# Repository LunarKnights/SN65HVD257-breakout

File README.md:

# Jetson CAN interface board
This board may be used to gain access to the CAN buses on the Jetson TX2 board, which aren't exposed on the carrier board we're currently using.
It mates in between the carrier board and the Jetson TX2, passing through all the connections, but tapping some lines off of the CAN pins and power supply to use in the SN65HVD256D CAN transceivers.
The CAN transceivers act essentially like level shifters, converting from the 3.3 V signals on the CAN RX/TX pins on the Jetson TX2 into the 5 V differential signal used in CAN.

`bom.xls` contains an Excel ordering list that should be usable at Mouser to reorder all the components except for the Samtec connectors.
Those need to be ordered off of the Samtec website, using the exact part names from the design.

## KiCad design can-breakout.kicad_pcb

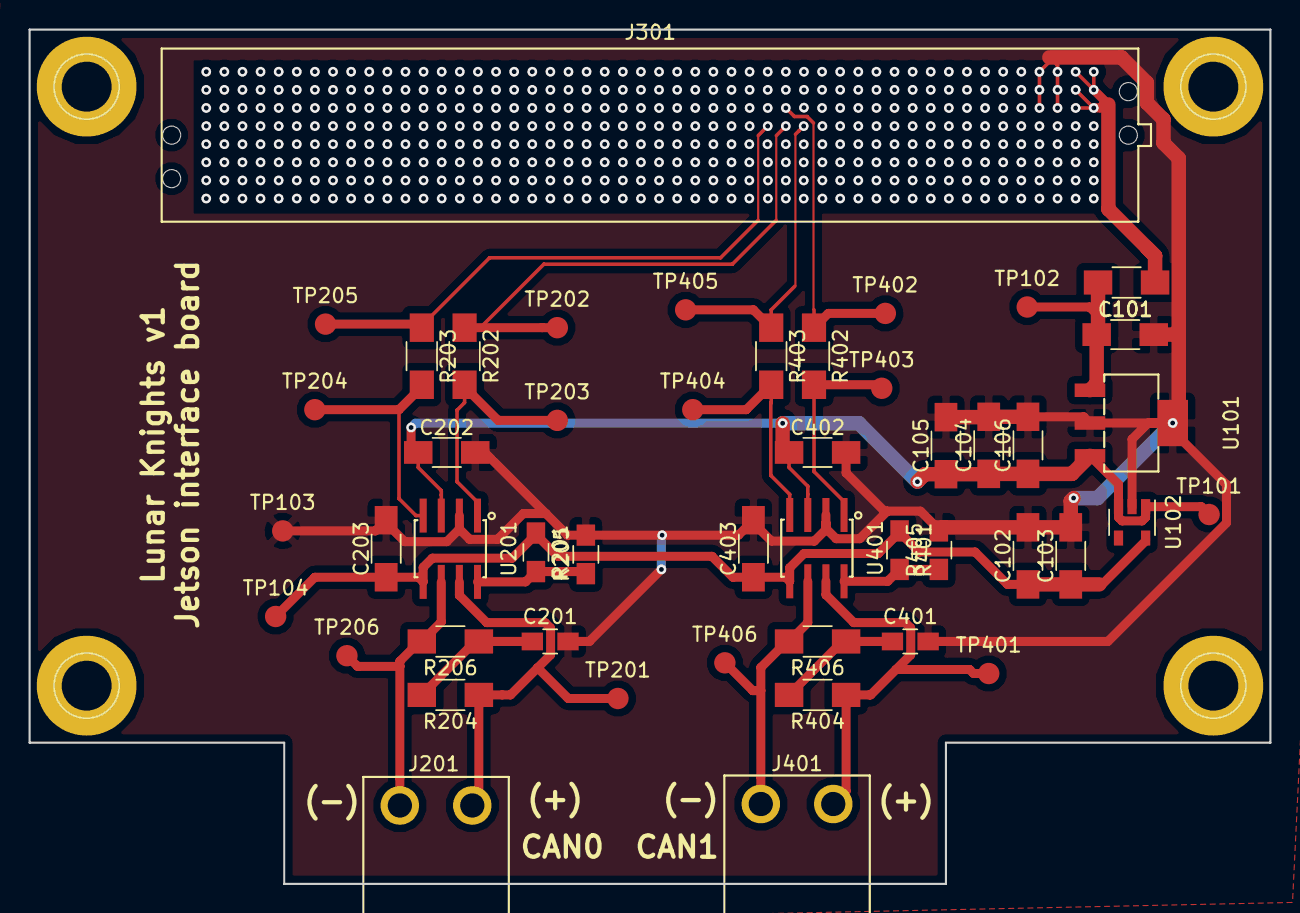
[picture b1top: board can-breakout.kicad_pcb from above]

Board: 2 copper layers, 87.0 x 59.9 mm, 49 parts (1 on the bottom side), 405 nets.

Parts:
C101, C102, C104, C105: 10u; C_1206_HandSoldering
C103, C106, C202, C203, C402, C403: 0u1; C_1206_HandSoldering
C201, C401: 10n; C_0805_HandSoldering
J201, J401: Screw_Terminal_01x02; 39532-0002
J301: SEAM-50-02.0-S-08-2-A-K-TR-ND; SEAM-50-02.0-S-08-2-A-K-TR
J302: SEAF-50-05.0-S-08-2-A-K-TR
L101: Ferrite; R_1206_HandSoldering
R201, R401: DNC; R_0805_HandSoldering
R202, R203, R402, R403: 4k7; R_1206_HandSoldering
R204, R206, R404, R406: 60; R_1206_HandSoldering
R205, R405: 10k; R_0805_HandSoldering
TP101, TP102, TP103, TP104, TP201, TP202, TP203, TP204, TP205, TP206, TP401, TP402, TP403, TP404, TP405, TP406: TEST; Measurement_Point_Round-SMD-Pad_Small
U101: UA78M05IDCYR; TI_SOT-223-4
U102: MIC5365-3.3YD5-TR; SOT-23-5
U201, U401: SN65HVD256; TI_SOIC8

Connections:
+3V3: C102.1, C103.1, C203.1, C403.1, R201.1, R401.1, TP104.1, U102.5, U201.5, U401.5
+5V: C104.1, C105.1, C106.1, C202.1, C402.1, TP101.1, U101.3, U102.1, U102.3, U201.3, U401.3
/CONNECTOR/CAN0_RX: J301.D19, J302.D19, R203.1, TP205.1
/CONNECTOR/CAN0_TX: J301.D18, J302.D18, R202.1, TP202.1
/CONNECTOR/CAN1_RX: J301.D17, J302.D17, R403.1, TP405.1
/CONNECTOR/CAN1_TX: J301.C18, J302.C18, R402.1, TP402.1
/CONNECTOR/VSUPPLY: J301.A1, J301.A2, J301.B1, J301.B2, J301.C1, J301.C2, J302.A1, J302.A2, J302.B1, J302.B2, J302.C1, J302.C2, L101.1
GND: C101.2, C102.2, C103.2, C104.2, C105.2, C106.2, C201.2, C202.2, C203.2, C401.2, C402.2, C403.2, J301.A3, J301.A4, J301.B3, J301.B4, J301.C3, J301.C4, J302.A3, J302.A4, J302.B3, J302.B4, J302.C3, J302.C4, R205.2, R405.2, TP103.1, U101.2, U101.4, U102.2, U201.2, U401.2
unnamed: C101.1, L101.2, TP102.1, U101.1
unnamed: C201.1, R204.2, R206.1
unnamed: C401.1, R404.2, R406.1
unnamed: J201.1, R204.1, TP201.1, U201.7
unnamed: J201.2, R206.2, TP206.1, U201.6
unnamed: J301.A5, J302.A5
unnamed: J301.A6, J302.A6
unnamed: J301.A7, J302.A7
unnamed: J301.A8, J302.A8
unnamed: J301.A9, J302.A9
unnamed: J301.A10, J302.A10
unnamed: J301.A11, J302.A11
unnamed: J301.A12, J302.A12
unnamed: J301.A13, J302.A13
unnamed: J301.A14, J302.A14
unnamed: J301.A15, J302.A15
unnamed: J301.A16, J302.A16
unnamed: J301.A17, J302.A17
unnamed: J301.A18, J302.A18
unnamed: J301.A19, J302.A19
unnamed: J301.A20, J302.A20
unnamed: J301.A21, J302.A21
unnamed: J301.A22, J302.A22
unnamed: J301.A23, J302.A23
unnamed: J301.A24, J302.A24
unnamed: J301.A25, J302.A25
unnamed: J301.A26, J302.A26
unnamed: J301.A27, J302.A27
unnamed: J301.A28, J302.A28
unnamed: J301.A29, J302.A29
unnamed: J301.A30, J302.A30
unnamed: J301.A31, J302.A31
unnamed: J301.A32, J302.A32
unnamed: J301.A33, J302.A33
unnamed: J301.A34, J302.A34
unnamed: J301.A35, J302.A35
unnamed: J301.A36, J302.A36
unnamed: J301.A37, J302.A37
unnamed: J301.A38, J302.A38
unnamed: J301.A39, J302.A39
unnamed: J301.A40, J302.A40
unnamed: J301.A41, J302.A41
unnamed: J301.A42, J302.A42
unnamed: J301.A43, J302.A43
unnamed: J301.A44, J302.A44
unnamed: J301.A45, J302.A45
unnamed: J301.A46, J302.A46
unnamed: J301.A47, J302.A47
unnamed: J301.A48, J302.A48
unnamed: J301.A49, J302.A49
unnamed: J301.A50, J302.A50
unnamed: J301.B5, J302.B5
unnamed: J301.B6, J302.B6
unnamed: J301.B7, J302.B7
unnamed: J301.B8, J302.B8
unnamed: J301.B9, J302.B9
unnamed: J301.B10, J302.B10
unnamed: J301.B11, J302.B11
unnamed: J301.B12, J302.B12
unnamed: J301.B13, J302.B13
unnamed: J301.B14, J302.B14
unnamed: J301.B15, J302.B15
unnamed: J301.B16, J302.B16
unnamed: J301.B17, J302.B17
unnamed: J301.B18, J302.B18
unnamed: J301.B19, J302.B19
unnamed: J301.B20, J302.B20
unnamed: J301.B21, J302.B21
unnamed: J301.B22, J302.B22
unnamed: J301.B23, J302.B23
unnamed: J301.B24, J302.B24
unnamed: J301.B25, J302.B25
unnamed: J301.B26, J302.B26
unnamed: J301.B27, J302.B27
unnamed: J301.B28, J302.B28
unnamed: J301.B29, J302.B29
unnamed: J301.B30, J302.B30
unnamed: J301.B31, J302.B31
unnamed: J301.B32, J302.B32
unnamed: J301.B33, J302.B33
unnamed: J301.B34, J302.B34
unnamed: J301.B35, J302.B35
unnamed: J301.B36, J302.B36
unnamed: J301.B37, J302.B37
unnamed: J301.B38, J302.B38
unnamed: J301.B39, J302.B39
unnamed: J301.B40, J302.B40
unnamed: J301.B41, J302.B41
unnamed: J301.B42, J302.B42
unnamed: J301.B43, J302.B43
unnamed: J301.B44, J302.B44
unnamed: J301.B45, J302.B45
unnamed: J301.B46, J302.B46
unnamed: J301.B47, J302.B47
unnamed: J301.B48, J302.B48
unnamed: J301.B49, J302.B49
unnamed: J301.B50, J302.B50
unnamed: J301.C5, J302.C5
unnamed: J301.C6, J302.C6
unnamed: J301.C7, J302.C7
unnamed: J301.C8, J302.C8
unnamed: J301.C9, J302.C9
unnamed: J301.C10, J302.C10
unnamed: J301.C11, J302.C11
unnamed: J301.C12, J302.C12
unnamed: J301.C13, J302.C13
unnamed: J301.C14, J302.C14
unnamed: J301.C15, J302.C15
unnamed: J301.C16, J302.C16
unnamed: J301.C17, J302.C17
unnamed: J301.C19, J302.C19
unnamed: J301.C20, J302.C20
unnamed: J301.C21, J302.C21
unnamed: J301.C22, J302.C22
unnamed: J301.C23, J302.C23
unnamed: J301.C24, J302.C24
unnamed: J301.C25, J302.C25
unnamed: J301.C26, J302.C26
unnamed: J301.C27, J302.C27
unnamed: J301.C28, J302.C28
unnamed: J301.C29, J302.C29
unnamed: J301.C30, J302.C30
unnamed: J301.C31, J302.C31
unnamed: J301.C32, J302.C32
unnamed: J301.C33, J302.C33
unnamed: J301.C34, J302.C34
unnamed: J301.C35, J302.C35
unnamed: J301.C36, J302.C36
unnamed: J301.C37, J302.C37
unnamed: J301.C38, J302.C38
unnamed: J301.C39, J302.C39
unnamed: J301.C40, J302.C40
unnamed: J301.C41, J302.C41
unnamed: J301.C42, J302.C42
unnamed: J301.C43, J302.C43
unnamed: J301.C44, J302.C44
unnamed: J301.C45, J302.C45
unnamed: J301.C46, J302.C46
unnamed: J301.C47, J302.C47
unnamed: J301.C48, J302.C48
unnamed: J301.C49, J302.C49
unnamed: J301.C50, J302.C50
unnamed: J301.D1, J302.D1
unnamed: J301.D2, J302.D2
unnamed: J301.D3, J302.D3
unnamed: J301.D4, J302.D4
unnamed: J301.D5, J302.D5
unnamed: J301.D6, J302.D6
unnamed: J301.D7, J302.D7
unnamed: J301.D8, J302.D8
unnamed: J301.D9, J302.D9
unnamed: J301.D10, J302.D10
unnamed: J301.D11, J302.D11
unnamed: J301.D12, J302.D12
unnamed: J301.D13, J302.D13
unnamed: J301.D14, J302.D14
unnamed: J301.D15, J302.D15
unnamed: J301.D16, J302.D16
unnamed: J301.D20, J302.D20
unnamed: J301.D21, J302.D21
unnamed: J301.D22, J302.D22
unnamed: J301.D23, J302.D23
unnamed: J301.D24, J302.D24
unnamed: J301.D25, J302.D25
unnamed: J301.D26, J302.D26
unnamed: J301.D27, J302.D27
unnamed: J301.D28, J302.D28
unnamed: J301.D29, J302.D29
unnamed: J301.D30, J302.D30
unnamed: J301.D31, J302.D31
unnamed: J301.D32, J302.D32
unnamed: J301.D33, J302.D33
unnamed: J301.D34, J302.D34
unnamed: J301.D35, J302.D35
unnamed: J301.D36, J302.D36
unnamed: J301.D37, J302.D37
unnamed: J301.D38, J302.D38
unnamed: J301.D39, J302.D39
unnamed: J301.D40, J302.D40
unnamed: J301.D41, J302.D41
unnamed: J301.D42, J302.D42
unnamed: J301.D43, J302.D43
unnamed: J301.D44, J302.D44
unnamed: J301.D45, J302.D45
unnamed: J301.D46, J302.D46
unnamed: J301.D47, J302.D47
unnamed: J301.D48, J302.D48
unnamed: J301.D49, J302.D49
unnamed: J301.D50, J302.D50
unnamed: J301.E1, J302.E1
unnamed: J301.E2, J302.E2
unnamed: J301.E3, J302.E3
unnamed: J301.E4, J302.E4
unnamed: J301.E5, J302.E5
unnamed: J301.E6, J302.E6
unnamed: J301.E7, J302.E7
unnamed: J301.E8, J302.E8
unnamed: J301.E9, J302.E9
unnamed: J301.E10, J302.E10
unnamed: J301.E11, J302.E11
unnamed: J301.E12, J302.E12
unnamed: J301.E13, J302.E13
unnamed: J301.E14, J302.E14
unnamed: J301.E15, J302.E15
unnamed: J301.E16, J302.E16
unnamed: J301.E17, J302.E17
unnamed: J301.E18, J302.E18
unnamed: J301.E19, J302.E19
unnamed: J301.E20, J302.E20
unnamed: J301.E21, J302.E21
unnamed: J301.E22, J302.E22
unnamed: J301.E23, J302.E23
unnamed: J301.E24, J302.E24
unnamed: J301.E25, J302.E25
unnamed: J301.E26, J302.E26
unnamed: J301.E27, J302.E27
unnamed: J301.E28, J302.E28
unnamed: J301.E29, J302.E29
unnamed: J301.E30, J302.E30
unnamed: J301.E31, J302.E31
unnamed: J301.E32, J302.E32
unnamed: J301.E33, J302.E33
unnamed: J301.E34, J302.E34
unnamed: J301.E35, J302.E35
unnamed: J301.E36, J302.E36
unnamed: J301.E37, J302.E37
unnamed: J301.E38, J302.E38
unnamed: J301.E39, J302.E39
unnamed: J301.E40, J302.E40
unnamed: J301.E41, J302.E41
unnamed: J301.E42, J302.E42
unnamed: J301.E43, J302.E43
unnamed: J301.E44, J302.E44
unnamed: J301.E45, J302.E45
unnamed: J301.E46, J302.E46
unnamed: J301.E47, J302.E47
unnamed: J301.E48, J302.E48
unnamed: J301.E49, J302.E49
unnamed: J301.E50, J302.E50
unnamed: J301.F1, J302.F1
unnamed: J301.F2, J302.F2
unnamed: J301.F3, J302.F3
unnamed: J301.F4, J302.F4
unnamed: J301.F5, J302.F5
unnamed: J301.F6, J302.F6
unnamed: J301.F7, J302.F7
unnamed: J301.F8, J302.F8
unnamed: J301.F9, J302.F9
unnamed: J301.F10, J302.F10
unnamed: J301.F11, J302.F11
unnamed: J301.F12, J302.F12
unnamed: J301.F13, J302.F13
unnamed: J301.F14, J302.F14
unnamed: J301.F15, J302.F15
unnamed: J301.F16, J302.F16
unnamed: J301.F17, J302.F17
unnamed: J301.F18, J302.F18
unnamed: J301.F19, J302.F19
unnamed: J301.F20, J302.F20
unnamed: J301.F21, J302.F21
unnamed: J301.F22, J302.F22
unnamed: J301.F23, J302.F23
unnamed: J301.F24, J302.F24
unnamed: J301.F25, J302.F25
unnamed: J301.F26, J302.F26
unnamed: J301.F27, J302.F27
unnamed: J301.F28, J302.F28
unnamed: J301.F29, J302.F29
unnamed: J301.F30, J302.F30
unnamed: J301.F31, J302.F31
unnamed: J301.F32, J302.F32
unnamed: J301.F33, J302.F33
unnamed: J301.F34, J302.F34
unnamed: J301.F35, J302.F35
unnamed: J301.F36, J302.F36
unnamed: J301.F37, J302.F37
unnamed: J301.F38, J302.F38
unnamed: J301.F39, J302.F39
unnamed: J301.F40, J302.F40
unnamed: J301.F41, J302.F41
unnamed: J301.F42, J302.F42
unnamed: J301.F43, J302.F43
unnamed: J301.F44, J302.F44
unnamed: J301.F45, J302.F45
unnamed: J301.F46, J302.F46
unnamed: J301.F47, J302.F47
unnamed: J301.F48, J302.F48
unnamed: J301.F49, J302.F49
unnamed: J301.F50, J302.F50
unnamed: J301.G1, J302.G1
unnamed: J301.G2, J302.G2
unnamed: J301.G3, J302.G3
unnamed: J301.G4, J302.G4
unnamed: J301.G5, J302.G5
unnamed: J301.G6, J302.G6
unnamed: J301.G7, J302.G7
unnamed: J301.G8, J302.G8
unnamed: J301.G9, J302.G9
unnamed: J301.G10, J302.G10
unnamed: J301.G11, J302.G11
unnamed: J301.G12, J302.G12
unnamed: J301.G13, J302.G13
unnamed: J301.G14, J302.G14
unnamed: J301.G15, J302.G15
unnamed: J301.G16, J302.G16
unnamed: J301.G17, J302.G17
unnamed: J301.G18, J302.G18
unnamed: J301.G19, J302.G19
unnamed: J301.G20, J302.G20
unnamed: J301.G21, J302.G21
unnamed: J301.G22, J302.G22
unnamed: J301.G23, J302.G23
unnamed: J301.G24, J302.G24
unnamed: J301.G25, J302.G25
unnamed: J301.G26, J302.G26
unnamed: J301.G27, J302.G27
unnamed: J301.G28, J302.G28
unnamed: J301.G29, J302.G29
unnamed: J301.G30, J302.G30
unnamed: J301.G31, J302.G31
unnamed: J301.G32, J302.G32
unnamed: J301.G33, J302.G33
unnamed: J301.G34, J302.G34
unnamed: J301.G35, J302.G35
unnamed: J301.G36, J302.G36
unnamed: J301.G37, J302.G37
unnamed: J301.G38, J302.G38
unnamed: J301.G39, J302.G39
unnamed: J301.G40, J302.G40
unnamed: J301.G41, J302.G41
unnamed: J301.G42, J302.G42
unnamed: J301.G43, J302.G43
unnamed: J301.G44, J302.G44
unnamed: J301.G45, J302.G45
unnamed: J301.G46, J302.G46
unnamed: J301.G47, J302.G47
unnamed: J301.G48, J302.G48
unnamed: J301.G49, J302.G49
unnamed: J301.G50, J302.G50
unnamed: J301.H1, J302.H1
unnamed: J301.H2, J302.H2
unnamed: J301.H3, J302.H3
unnamed: J301.H4, J302.H4
unnamed: J301.H5, J302.H5
unnamed: J301.H6, J302.H6
unnamed: J301.H7, J302.H7
unnamed: J301.H8, J302.H8
unnamed: J301.H9, J302.H9
unnamed: J301.H10, J302.H10
unnamed: J301.H11, J302.H11
unnamed: J301.H12, J302.H12
unnamed: J301.H13, J302.H13
unnamed: J301.H14, J302.H14
unnamed: J301.H15, J302.H15
unnamed: J301.H16, J302.H16
unnamed: J301.H17, J302.H17
unnamed: J301.H18, J302.H18
unnamed: J301.H19, J302.H19
unnamed: J301.H20, J302.H20
unnamed: J301.H21, J302.H21
unnamed: J301.H22, J302.H22
unnamed: J301.H23, J302.H23
unnamed: J301.H24, J302.H24
unnamed: J301.H25, J302.H25
unnamed: J301.H26, J302.H26
unnamed: J301.H27, J302.H27
unnamed: J301.H28, J302.H28
unnamed: J301.H29, J302.H29
unnamed: J301.H30, J302.H30
unnamed: J301.H31, J302.H31
unnamed: J301.H32, J302.H32
unnamed: J301.H33, J302.H33
unnamed: J301.H34, J302.H34
unnamed: J301.H35, J302.H35
unnamed: J301.H36, J302.H36
unnamed: J301.H37, J302.H37
unnamed: J301.H38, J302.H38
unnamed: J301.H39, J302.H39
unnamed: J301.H40, J302.H40
unnamed: J301.H41, J302.H41
unnamed: J301.H42, J302.H42
unnamed: J301.H43, J302.H43
unnamed: J301.H44, J302.H44
unnamed: J301.H45, J302.H45
unnamed: J301.H46, J302.H46
unnamed: J301.H47, J302.H47
unnamed: J301.H48, J302.H48
unnamed: J301.H49, J302.H49
unnamed: J301.H50, J302.H50
unnamed: J401.1, R404.1, TP401.1, U401.7
unnamed: J401.2, R406.2, TP406.1, U401.6
unnamed: R201.2, R205.1, U201.8
unnamed: R202.2, TP203.1, U201.1
unnamed: R203.2, TP204.1, U201.4
unnamed: R401.2, R405.1, U401.8
unnamed: R402.2, TP403.1, U401.1
unnamed: R403.2, TP404.1, U401.4

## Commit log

2017-11-18 Save work for attendance check
2017-11-18 Add schematic PDF
2017-11-18 Start work on CAN layout
2017-11-18 Add datasheet for connector
2017-11-20 Start work on library part for SEAM connector
2017-11-20 Make library files for both connectors and wire them together
2017-11-20 python gen-seam-fp.py > breakout.pretty/SEAM-50-02.0-S-08-2-A-K-TR.kicad_mod; python gen-seaf-fp.py > breakout.pretty/SEAF-50-05.0-S-08-2-A-K-TR.kicad_mod
2017-11-20 Add vias and ground connections
2017-11-20 Add hierarchial pins for CAN, TODO regen netlist
2018-01-08 Add some protection diodes, connect most things up TODO add TVS diodes to CAN bus terinals
2018-01-09 Module outline added to PCB, first CAN bus added
2018-01-10 Parts laid out, only routing left
2018-01-13 Finish layout and generate Gerber files
2018-01-13 Update PDFs
2018-01-13 Add silkscreen markings
2018-01-13 Add Gerber zipfile and BOM; grep value can-breakout.net | sort | tr -d ' ' | cut -c 7- | rev | cut -c 2- | rev | uniq -c > bom
2018-01-13 Remove binaries from project; try to release-based stuff instead
2018-01-13 Add orderable BOM and README
